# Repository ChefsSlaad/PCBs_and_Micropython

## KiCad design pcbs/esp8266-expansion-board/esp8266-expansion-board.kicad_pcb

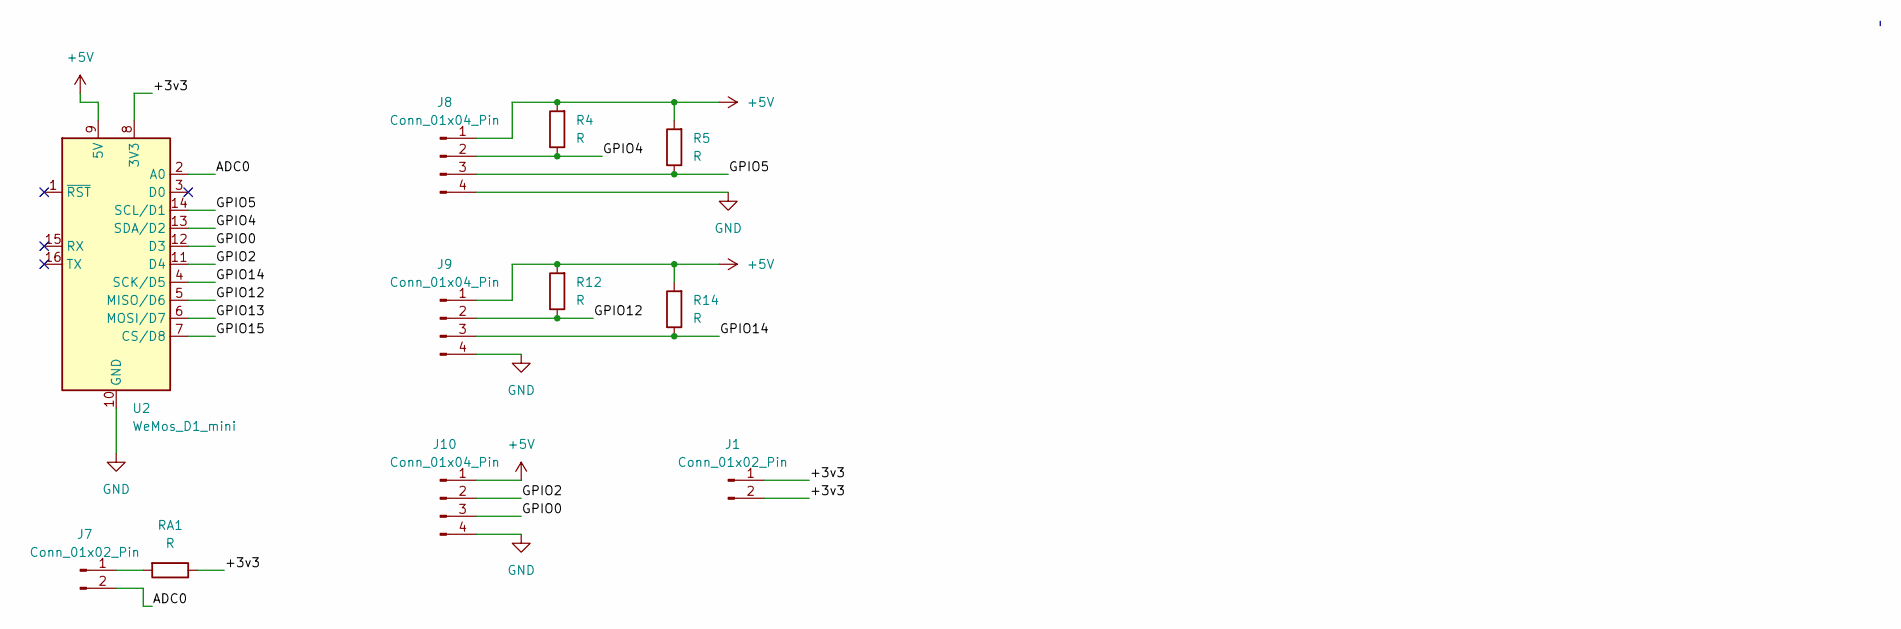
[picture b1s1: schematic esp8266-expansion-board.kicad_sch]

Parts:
J1, J7: Conn_01x02_Pin; PinHeader_1x02_P2.54mm_Vertical
J8, J9, J10: Conn_01x04_Pin; PinHeader_1x04_P2.54mm_Vertical
R4, R5, R12, R14: R; R_Axial_DIN0207_L6.3mm_D2.5mm_P7.62mm_Horizontal
RA1: R; R_Axial_DIN0207_L6.3mm_D2.5mm_P7.62mm_Horizontal
U2: WeMos_D1_mini; WEMOS_D1_mini_light

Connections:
+5V: J8.1, J9.1, J10.1, R4.2, R5.2, R12.2, R14.2, U2.9 (5V)
/+3v3: J1.1, J1.2, RA1.1, U2.8 (3V3)
/ADC0: J7.2, U2.2 (A0)
/GPIO0: J10.3, U2.12 (D3)
/GPIO2: J10.2, U2.11 (D4)
/GPIO4: J8.2, R4.1, U2.13 (SDA/D2)
/GPIO5: J8.3, R5.1, U2.14 (SCL/D1)
/GPIO12: J9.2, R12.1, U2.5 (MISO/D6)
/GPIO13: U2.6 (MOSI/D7)
/GPIO14: J9.3, R14.1, U2.4 (SCK/D5)
/GPIO15: U2.7 (CS/D8)
GND: J8.4, J9.4, J10.4, U2.10 (GND)
unnamed: J7.1, RA1.2

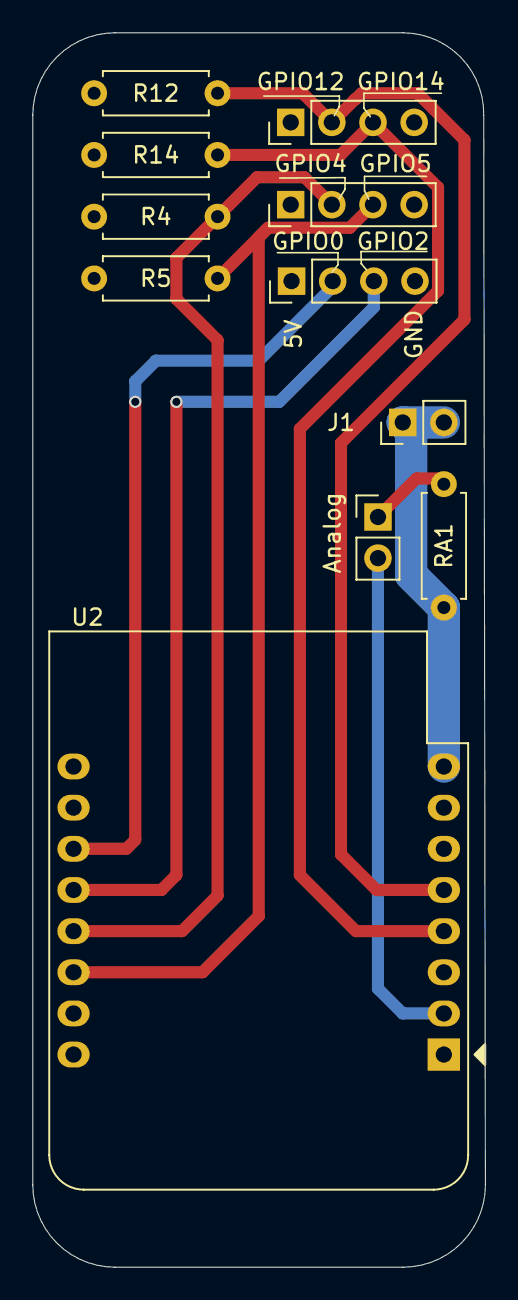
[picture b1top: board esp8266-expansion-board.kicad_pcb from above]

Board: 2 copper layers, 27.9 x 76.2 mm, 11 parts (0 on the bottom side), 11 nets.

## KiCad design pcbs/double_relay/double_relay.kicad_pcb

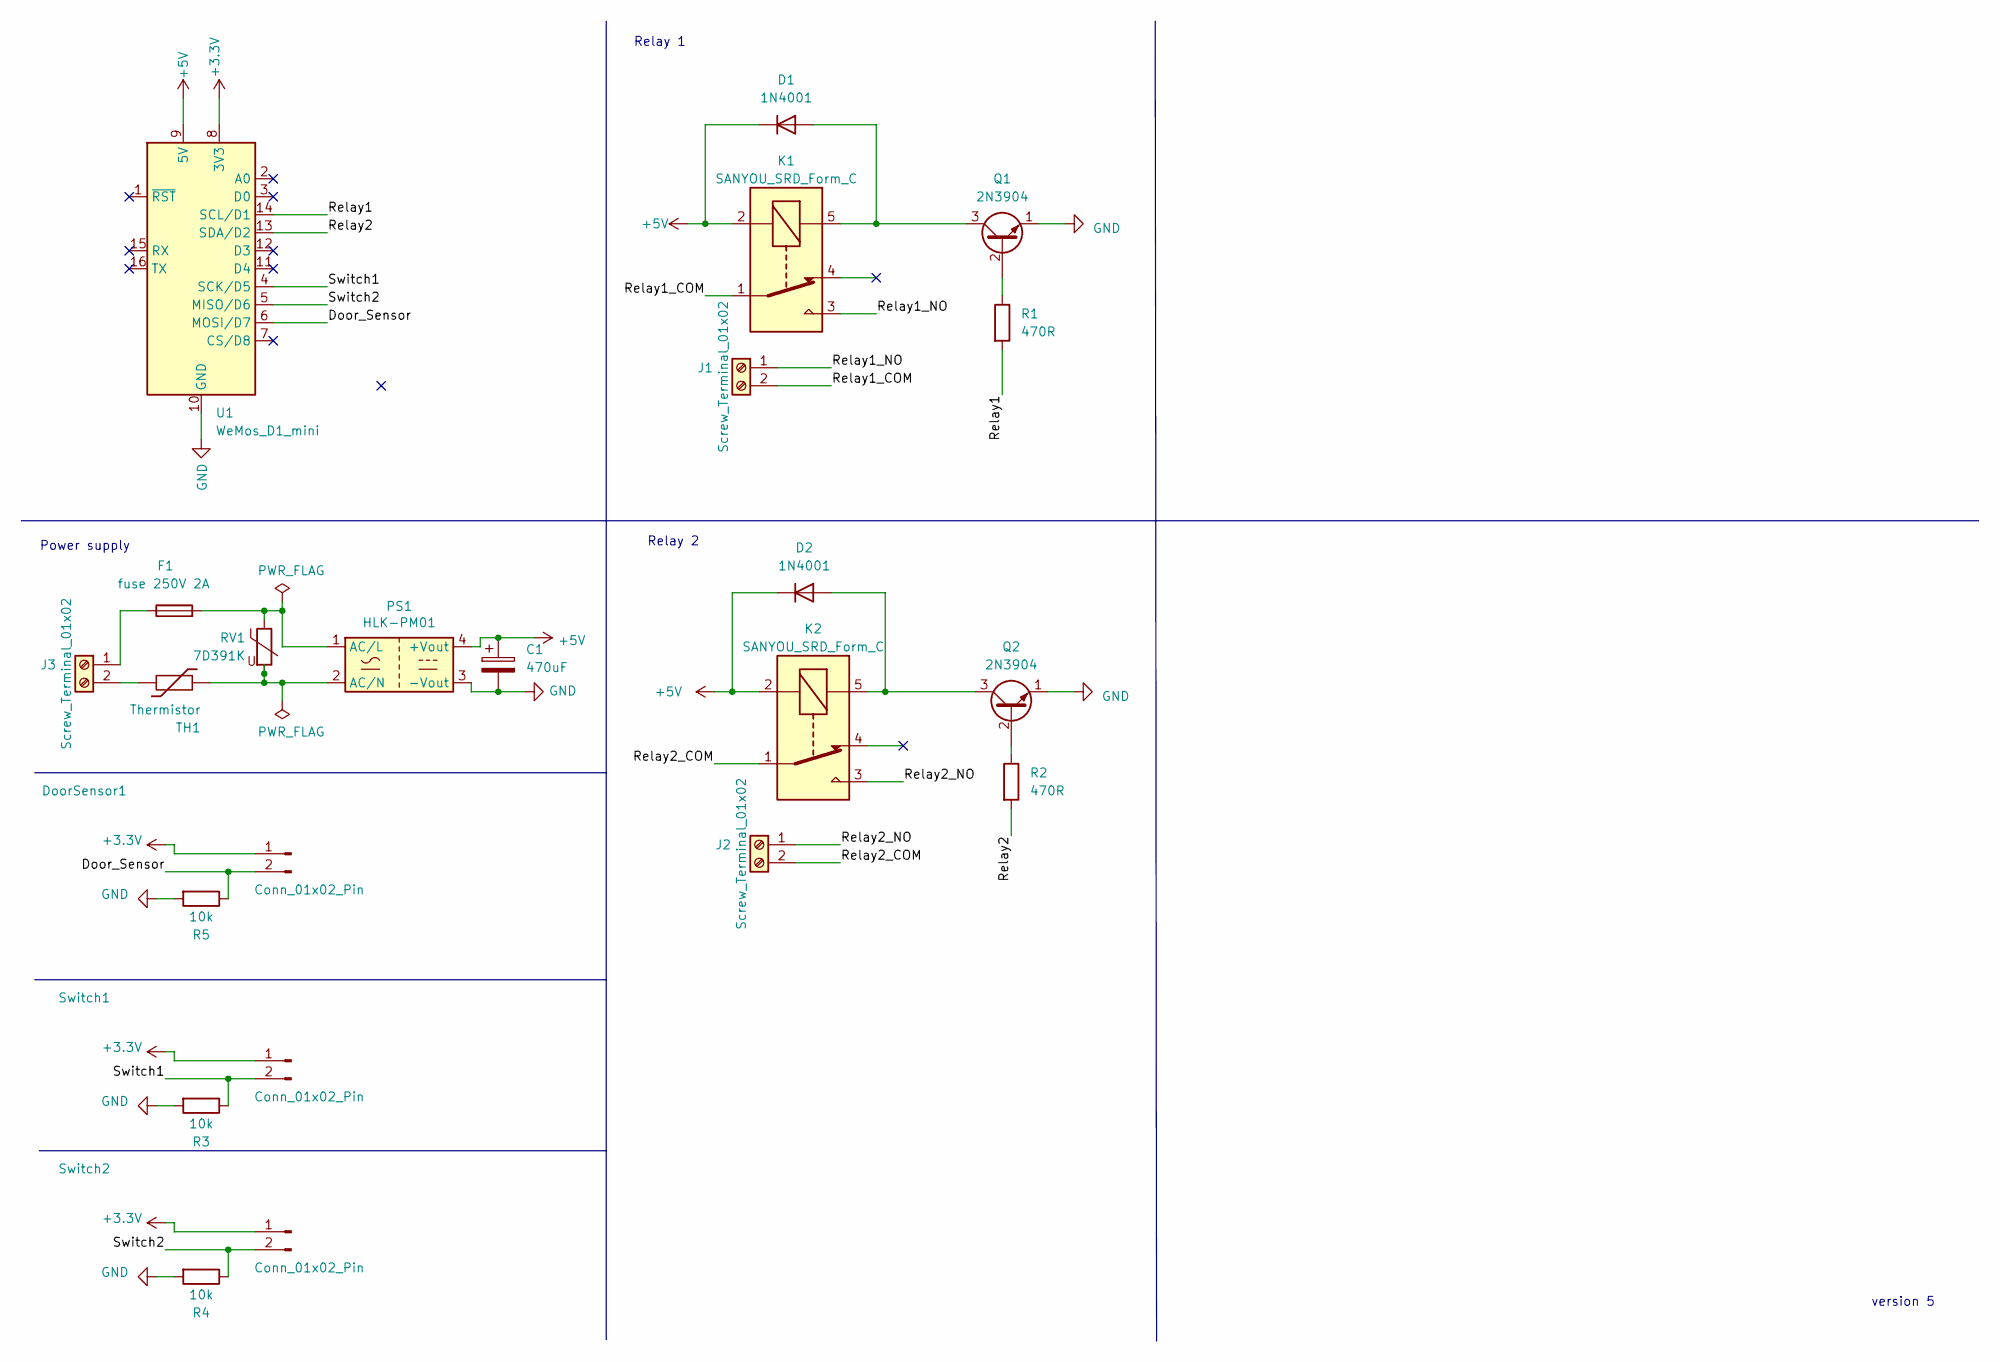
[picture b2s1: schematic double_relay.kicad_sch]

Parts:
C1: 470uF; CP_Radial_D6.3mm_P2.50mm
D1, D2: 1N4001; D_DO-41_SOD81_P7.62mm_Horizontal
DoorSensor1: Conn_01x02_Pin; JST_EH_B2B-EH-A_1x02_P2.50mm_Vertical
F1: fuse 250V 2A; resetable_fuse_D9mm_W3.3mm_P5mm
J1, J2, J3: Screw_Terminal_01x02; TerminalBlock_bornier-2_P5.08mm
K1, K2: SANYOU_SRD_Form_C; Relay_SPDT_SANYOU_SRD_Series_Form_C
PS1: HLK-PM01; Converter_ACDC_HiLink_HLK-PMxx
Q1, Q2: 2N3904; TO-92_Wide
R1, R2: 470R; R_Axial_DIN0207_L6.3mm_D2.5mm_P7.62mm_Horizontal
R3, R4, R5: 10k; R_Axial_DIN0207_L6.3mm_D2.5mm_P7.62mm_Horizontal
RV1: 7D391K; resetable_fuse_D9mm_W3.3mm_P5mm
Switch1, Switch2: Conn_01x02_Pin; JST_EH_B2B-EH-A_1x02_P2.50mm_Vertical
TH1: Thermistor; R_Axial_DIN0414_L11.9mm_D4.5mm_P15.24mm_Horizontal
U1: WeMos_D1_mini; WEMOS_D1_mini_light

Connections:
+3.3V: DoorSensor1.1, Switch1.1, Switch2.1, U1.8 (3V3)
+5V: C1.1, D1.1 (K), D2.1 (K), K1.2, K2.2, PS1.4 (+Vout), U1.9 (5V)
/Door_Sensor: DoorSensor1.2, R5.1, U1.6 (MOSI/D7)
/Relay1: R1.2, U1.14 (SCL/D1)
/Relay1_COM: J1.2, K1.1
/Relay1_NO: J1.1, K1.3
/Relay2: R2.2, U1.13 (SDA/D2)
/Relay2_COM: J2.2, K2.1
/Relay2_NO: J2.1, K2.3
/Switch1: R3.1, Switch1.2, U1.4 (SCK/D5)
/Switch2: R4.1, Switch2.2, U1.5 (MISO/D6)
GND: C1.2, PS1.3 (-Vout), Q1.1 (E), Q2.1 (E), R3.2, R4.2, R5.2, U1.10 (GND)
unnamed: D1.2 (A), K1.5, Q1.3 (C)
unnamed: D2.2 (A), K2.5, Q2.3 (C)
unnamed: F1.1, J3.1
unnamed: J3.2, TH1.2
unnamed: F1.2, PS1.1 (AC/L), RV1.1
unnamed: PS1.2 (AC/N), RV1.2, TH1.1
unnamed: Q1.2 (B), R1.1
unnamed: Q2.2 (B), R2.1

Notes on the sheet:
Power supply
Relay 2
version 5
Relay 1

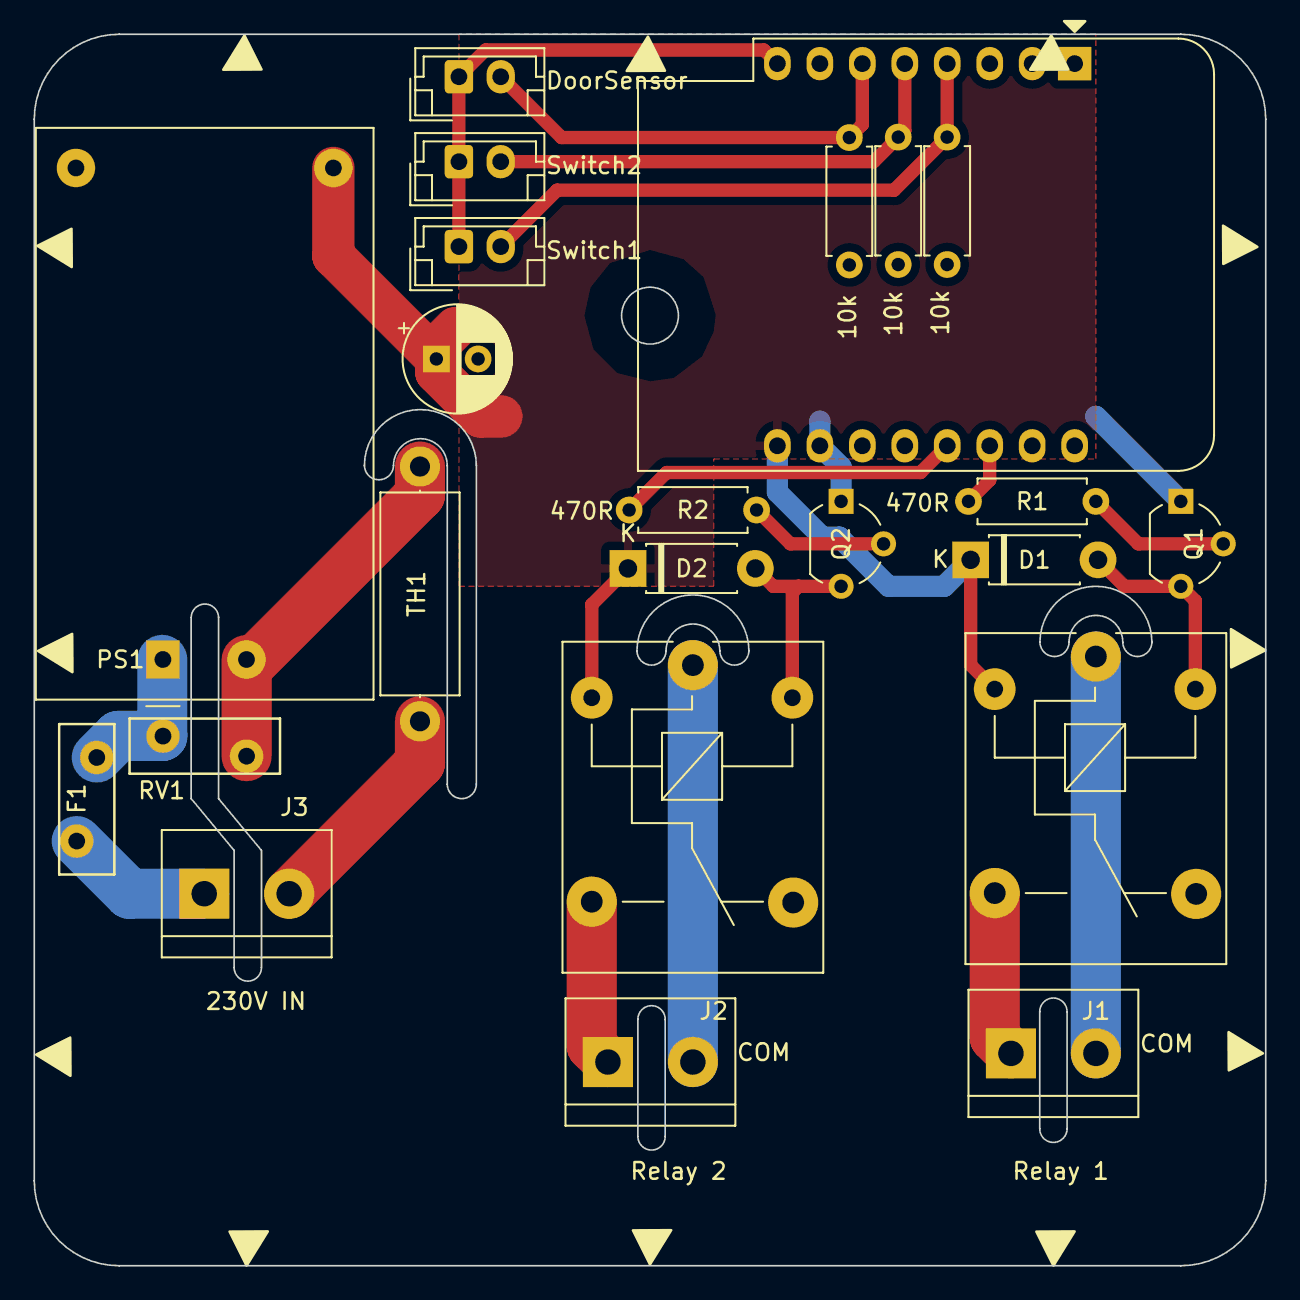
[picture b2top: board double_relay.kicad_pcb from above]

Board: 2 copper layers, 73.7 x 73.7 mm, 23 parts (0 on the bottom side), 20 nets.

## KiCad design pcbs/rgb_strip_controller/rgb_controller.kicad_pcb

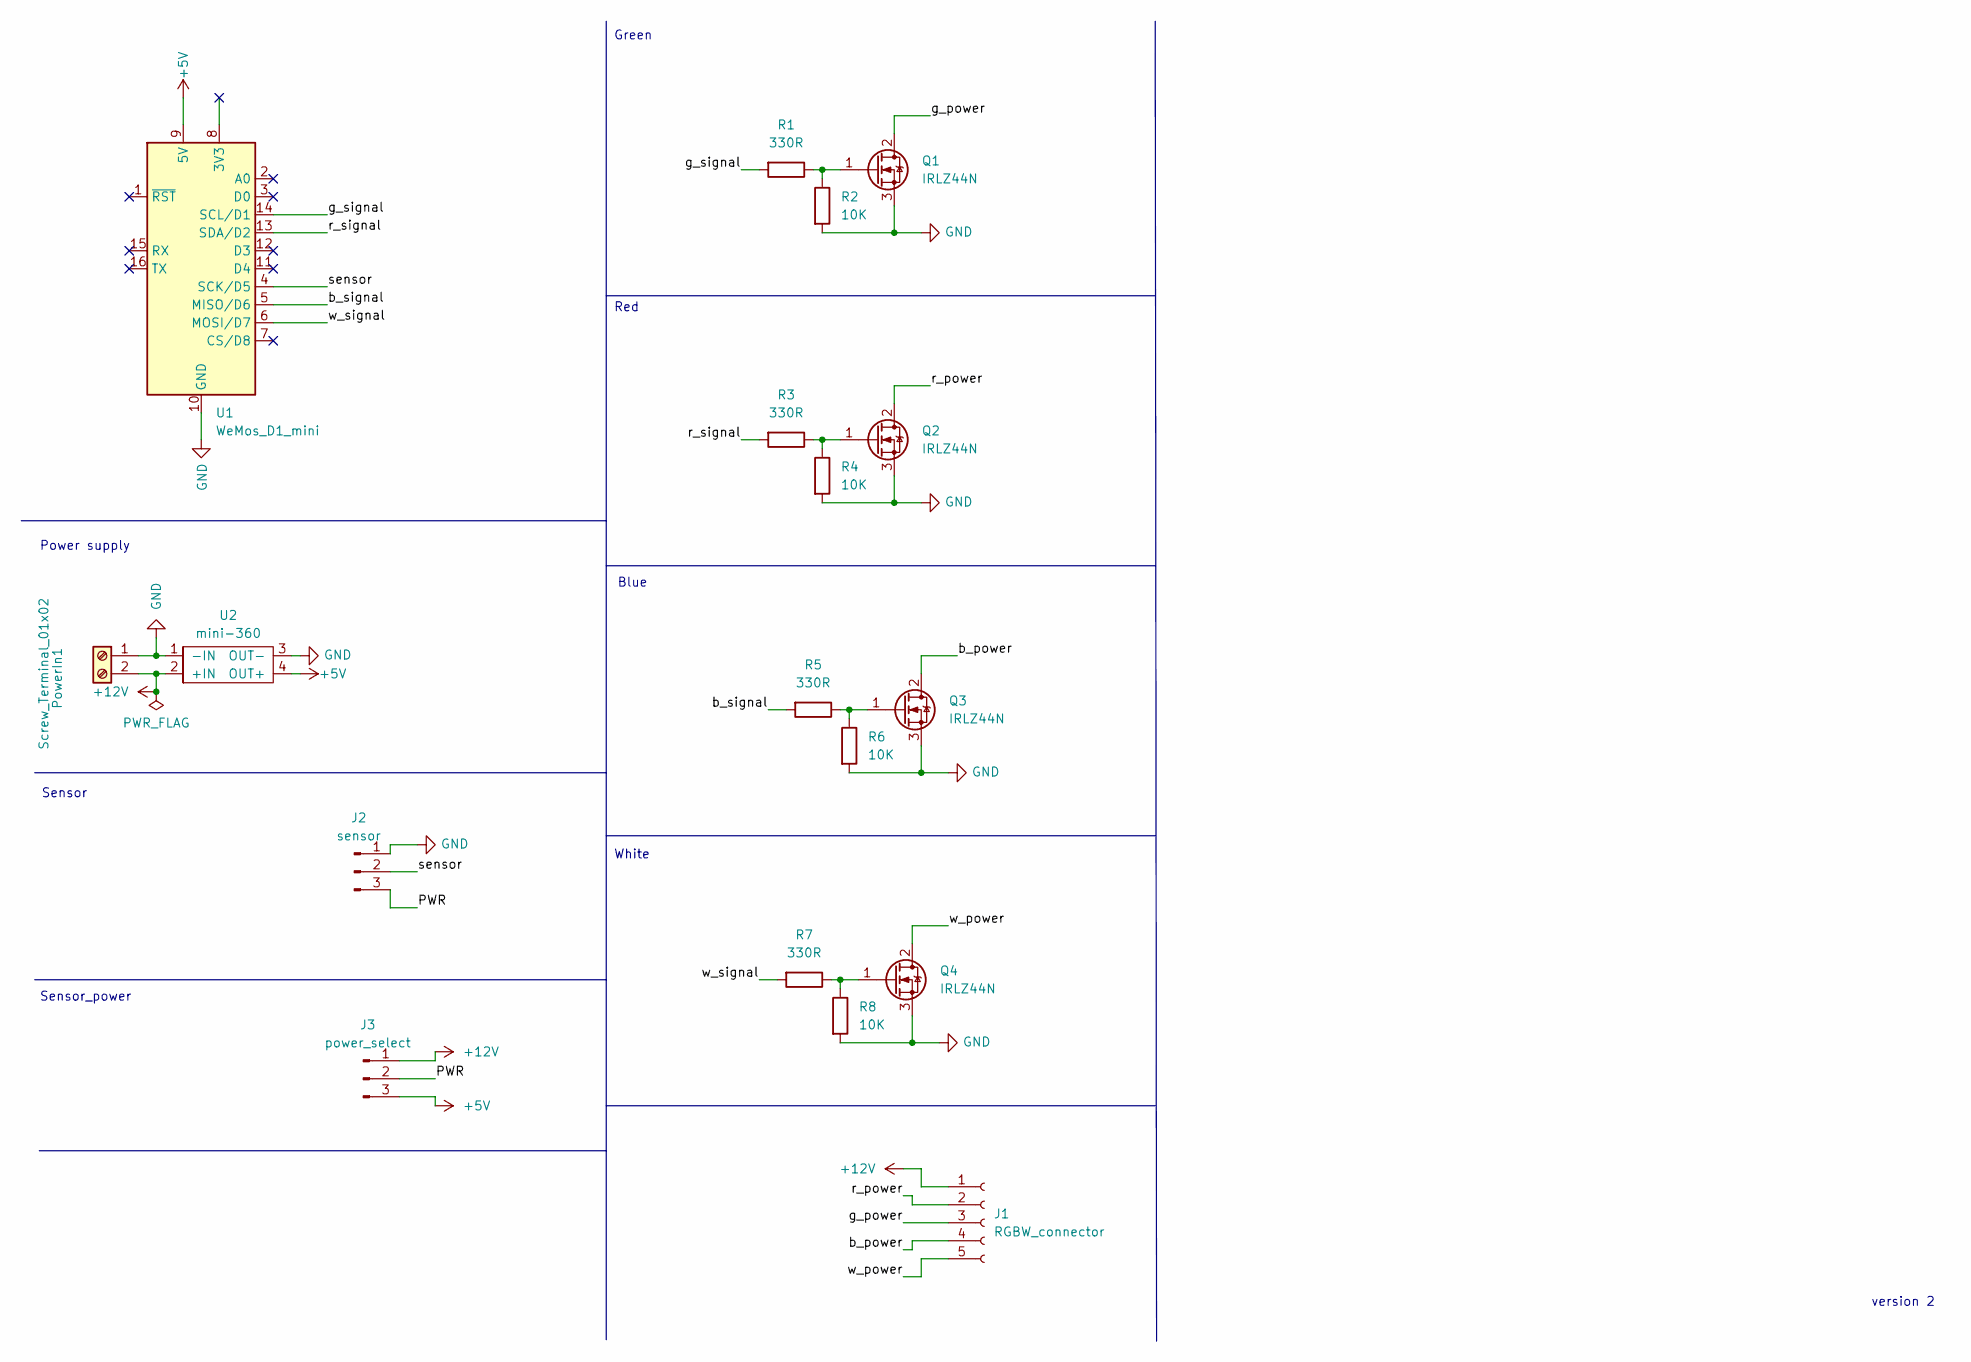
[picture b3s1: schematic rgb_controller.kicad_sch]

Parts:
J1: RGBW_connector; JST_EH_B5B-EH-A_1x05_P2.50mm_Vertical
J2: sensor; JST_EH_B3B-EH-A_1x03_P2.50mm_Vertical
J3: power_select; PinHeader_1x03_P2.54mm_Vertical
PowerIn1: Screw_Terminal_01x02; TerminalBlock_bornier-2_P5.08mm
Q1, Q2, Q3, Q4: IRLZ44N; TO-220-3_Vertical
R1, R3, R5, R7: 330R; R_Axial_DIN0207_L6.3mm_D2.5mm_P7.62mm_Horizontal
R2, R4, R6, R8: 10K; R_Axial_DIN0204_L3.6mm_D1.6mm_P2.54mm_Vertical
U1: WeMos_D1_mini; WEMOS_D1_mini_light
U2: mini-360; buck_converter 16.8x22,14

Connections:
+5V: J3.3, U1.9 (5V), U2.4 (OUT+)
+12V: J1.1, J3.1, PowerIn1.2, U2.2 (+IN)
/PWR: J2.3, J3.2
/b_power: J1.4, Q3.2 (D)
/b_signal: R5.2, U1.5 (MISO/D6)
/g_power: J1.3, Q1.2 (D)
/g_signal: R1.2, U1.14 (SCL/D1)
/r_power: J1.2, Q2.2 (D)
/r_signal: R3.2, U1.13 (SDA/D2)
/sensor: J2.2, U1.4 (SCK/D5)
/w_power: J1.5, Q4.2 (D)
/w_signal: R7.2, U1.6 (MOSI/D7)
GND: J2.1, PowerIn1.1, Q1.3 (S), Q2.3 (S), Q3.3 (S), Q4.3 (S), R2.2, R4.2, R6.2, R8.2, U1.10 (GND), U2.1 (-IN), U2.3 (OUT-)
unnamed: Q1.1 (G), R1.1, R2.1
unnamed: Q2.1 (G), R3.1, R4.1
unnamed: Q3.1 (G), R5.1, R6.1
unnamed: Q4.1 (G), R7.1, R8.1

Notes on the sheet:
Power supply
Red
Sensor
Sensor_power
Blue
White
version 2
Green

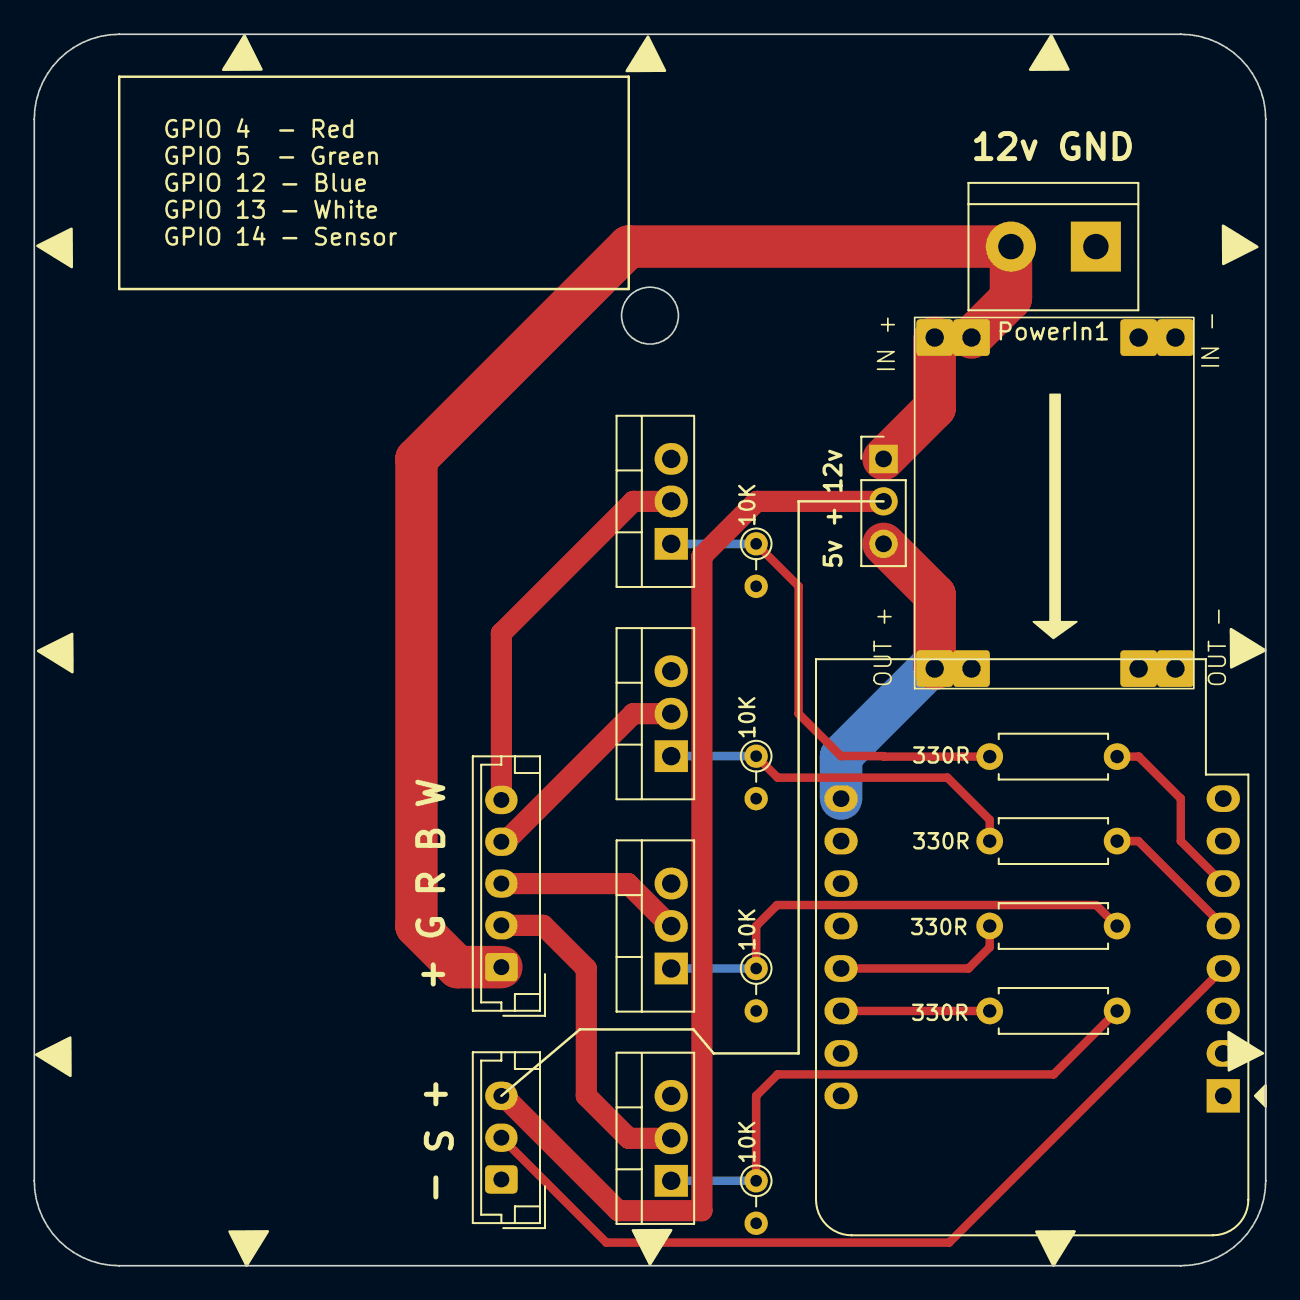
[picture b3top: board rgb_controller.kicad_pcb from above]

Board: 2 copper layers, 73.7 x 73.7 mm, 18 parts (0 on the bottom side), 17 nets.

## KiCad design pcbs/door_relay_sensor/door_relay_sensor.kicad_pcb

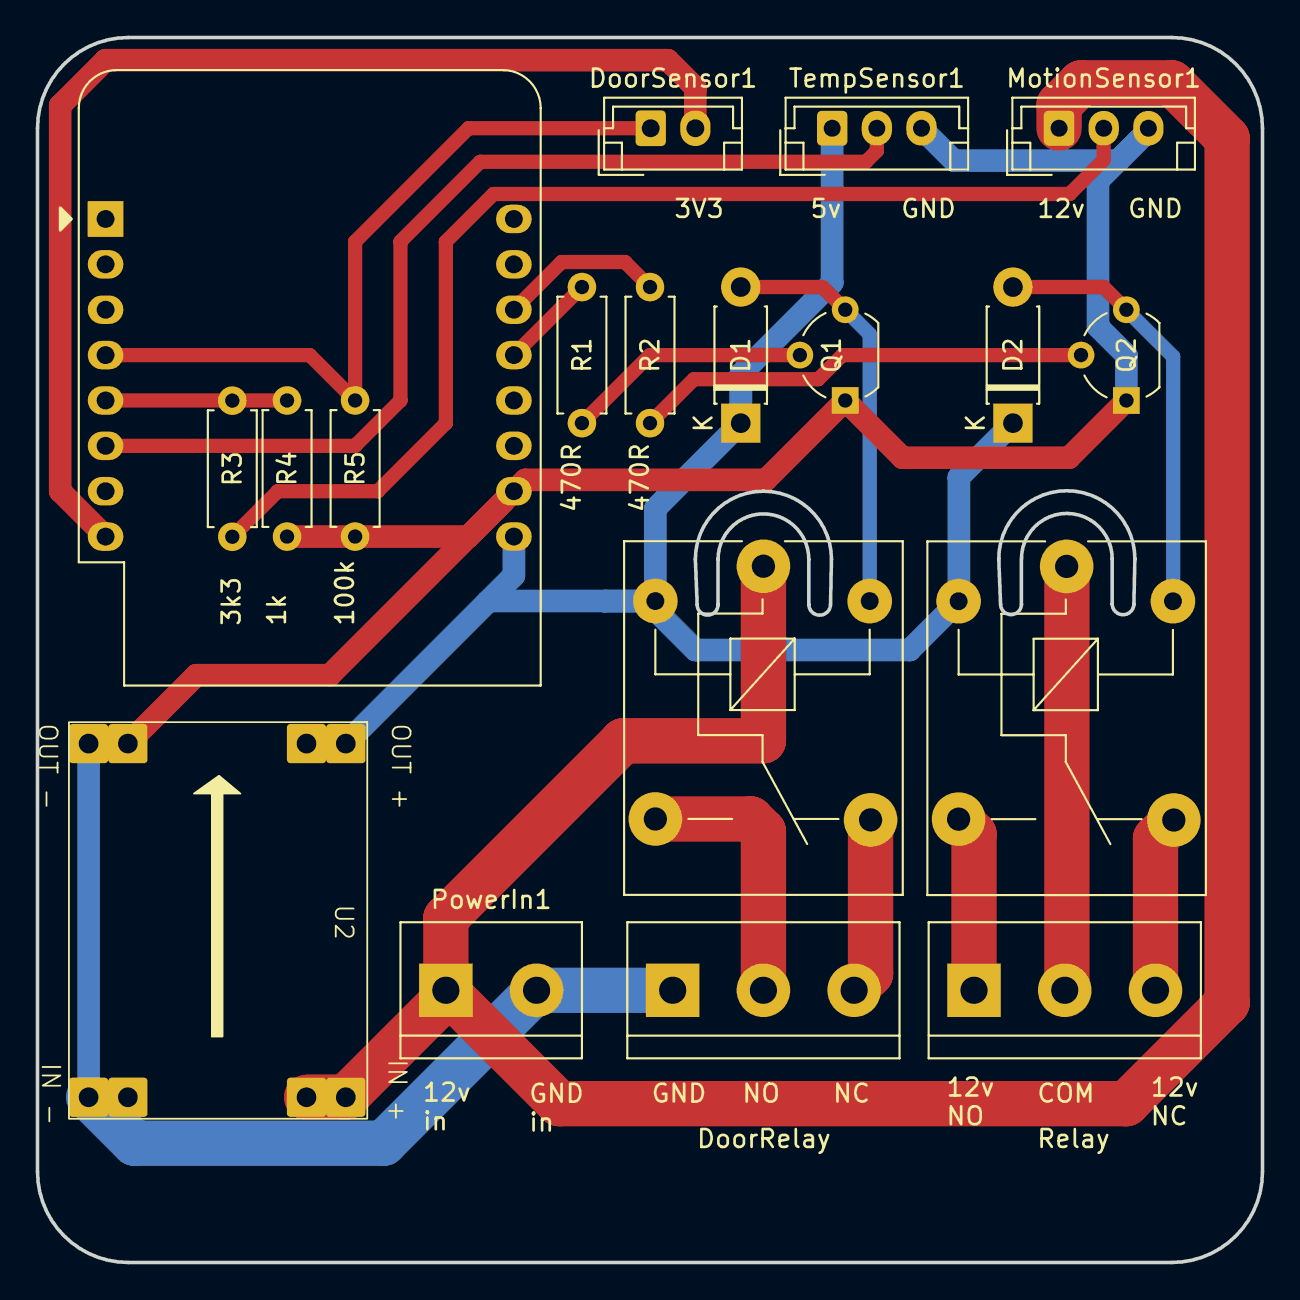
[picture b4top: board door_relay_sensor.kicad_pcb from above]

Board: 2 copper layers, 68.6 x 68.6 mm, 19 parts (0 on the bottom side), 19 nets.

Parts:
D1, D2: 1N4001; D_DO-41_SOD81_P7.62mm_Horizontal
DoorRelay1: Screw_Terminal_01x03; TerminalBlock_bornier-3_P5.08mm
DoorSensor1: Conn_01x02_Pin; JST_EH_B2B-EH-A_1x02_P2.50mm_Vertical
K1, K2: SANYOU_SRD_Form_C; Relay_SPDT_SANYOU_SRD_Series_Form_C
MotionSensor1: Conn_01x03_Pin; JST_EH_B3B-EH-A_1x03_P2.50mm_Vertical
PowerIn1: Screw_Terminal_01x02; TerminalBlock_bornier-2_P5.08mm
Q1, Q2: 2N3904; TO-92_Wide
R1, R2, R4: 1K; R_Axial_DIN0207_L6.3mm_D2.5mm_P7.62mm_Horizontal
R3: 3K3; R_Axial_DIN0207_L6.3mm_D2.5mm_P7.62mm_Horizontal
R5: 100k; R_Axial_DIN0207_L6.3mm_D2.5mm_P7.62mm_Horizontal
Relay1: Screw_Terminal_01x03; TerminalBlock_bornier-3_P5.08mm
TempSensor1: Conn_01x03_Pin; JST_EH_B3B-EH-A_1x03_P2.50mm_Vertical
U1: WeMos_D1_mini; WEMOS_D1_mini_light
U2: mini-360; buck_converter 16.8x22,14

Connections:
+3.3V: DoorSensor1.2, U1.8 (3V3)
+5V: D1.1 (K), D2.1 (K), K1.2, K2.2, TempSensor1.1, U1.9 (5V), U2.4 (OUT+)
+12V: K1.1, MotionSensor1.1, PowerIn1.1, U2.2 (+IN)
/Door_Sensor: DoorSensor1.1, R5.1, U1.4 (SCK/D5)
/Motion_Sensor: R3.2, R4.2, U1.5 (MISO/D6)
/R2_COM: K2.1, Relay1.2
/R2_NC: K2.4, Relay1.3
/R2_NO: K2.3, Relay1.1
/Relay1: R1.2, U1.13 (SDA/D2)
/Relay1_NC: DoorRelay1.3, K1.4
/Relay1_NO: DoorRelay1.2, K1.3
/Relay2: R2.2, U1.14 (SCL/D1)
/Temp_Sensor: TempSensor1.2, U1.6 (MOSI/D7)
GND: DoorRelay1.1, MotionSensor1.3, PowerIn1.2, Q1.1 (E), Q2.1 (E), R4.1, R5.2, TempSensor1.3, U1.10 (GND), U2.1 (-IN), U2.3 (OUT-)
unnamed: D1.2 (A), K1.5, Q1.3 (C)
unnamed: D2.2 (A), K2.5, Q2.3 (C)
unnamed: MotionSensor1.2, R3.1
unnamed: Q1.2 (B), R1.1
unnamed: Q2.2 (B), R2.1

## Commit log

2024-12-21 new sensor pcb
